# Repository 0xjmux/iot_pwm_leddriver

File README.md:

# IoT driver for "Dumb" 5050 RGB LED Strips
ESP8266-based LED Driver designed to work with WLED and cheap 12V barrel-jack power supplies for accent lighting around the home. 

This driver was designed to allow network-enabled control of almost any 12V "dumb" strip around, from plain white to FCOB strips to RGBW. 

My v1.0 worked perfectly, so I'm going to leave it as-is. The only upgrades I'd make at this point are: 
1) WLED announced that they're deprecating ESP8266 support right after I ordered v1.0, but for driving a single color the ESP8266 should be more than enough. 
2) There's some whine from the Power mosfet drivers, but it's barely noticable and not really worth addressing unless I was already doing a redesign. 

***See [Releases](https://github.com/0xjmux/iot_pwm_leddriver/releases) for all the necessary files and information to make your own!***

### Features
* Uses mini blade fuses for overcurrent protection and to protect against fire hazard from shorts on bad quality LED strips
* Board designed to handle up to and above maximum expected from most LED strips (8A)
* 4 channels to handle RGBW: or up to 4 single-color strips
* Terminal block for ease of use connecting strips and a 2.1mm jack allowing use of cheap 12V supplies you have lying around
* Capable of both programming and debug over [SOICbite Connector](https://github.com/SimonMerrett/SOICbite).
* Includes status and power LEDs and board overvoltage protection

* See [ABOUT.md](./ABOUT.md) for some information about design goals and the project. 

#### Pinout 

| Output     | ESP Pin |
| -----      | ------  |
| LED_R      | GPIO 5  |
| LED_G      | GPIO 13 |
| LED_B      | GPIO 14 |
| LED_W      | GPIO 12 |
| STATUS LED | GPIO 16 |

#### Case
I also designed a 3D printable case, which can be found under [case/](case/). The screw terminals are still easily accessible, and there's a window on the bottom so you can see the board name and version without having to open it. 
* The case uses M2x8mm screws to hold the two halves together, and is designed to be printed in PLA with 10% infill. 

### v1.0 - First try works!
* Complete redesign from v0.2, with a focus on overall system design and ease of setup for the end user. 
* Uses mini blade fuses for overcurrent protection and to protect against fire hazard from shorts on bad quality LED strips
* Board designed to handle up to and above maximum expected from most LED strips (8A)
* 4 channels to handle RGBW: or up to 4 single-color strips
* Terminal block for ease of use connecting strips and a 2.1mm jack allowing use of cheap 12V supplies you have lying around
* Capable of both programming and debug over [SOICbite Connector](https://github.com/SimonMerrett/SOICbite).
* Includes status and power LEDs and board overvoltage protection

### v0.1 - Quick Board Mock-up
* My first 4 layer board! But some improvement still possible

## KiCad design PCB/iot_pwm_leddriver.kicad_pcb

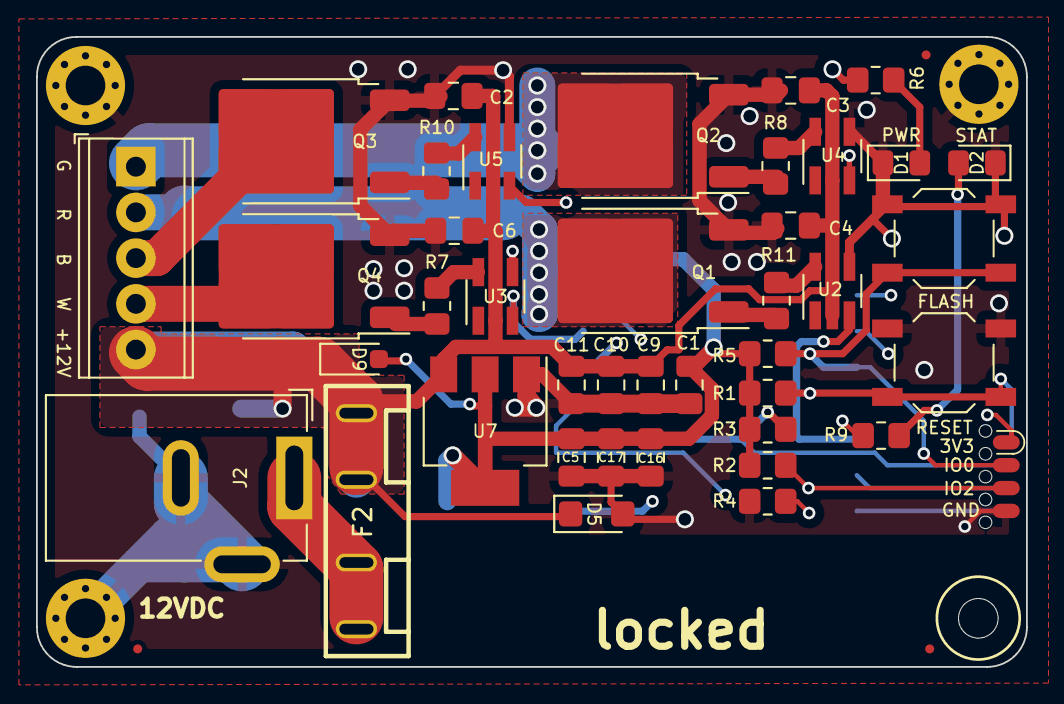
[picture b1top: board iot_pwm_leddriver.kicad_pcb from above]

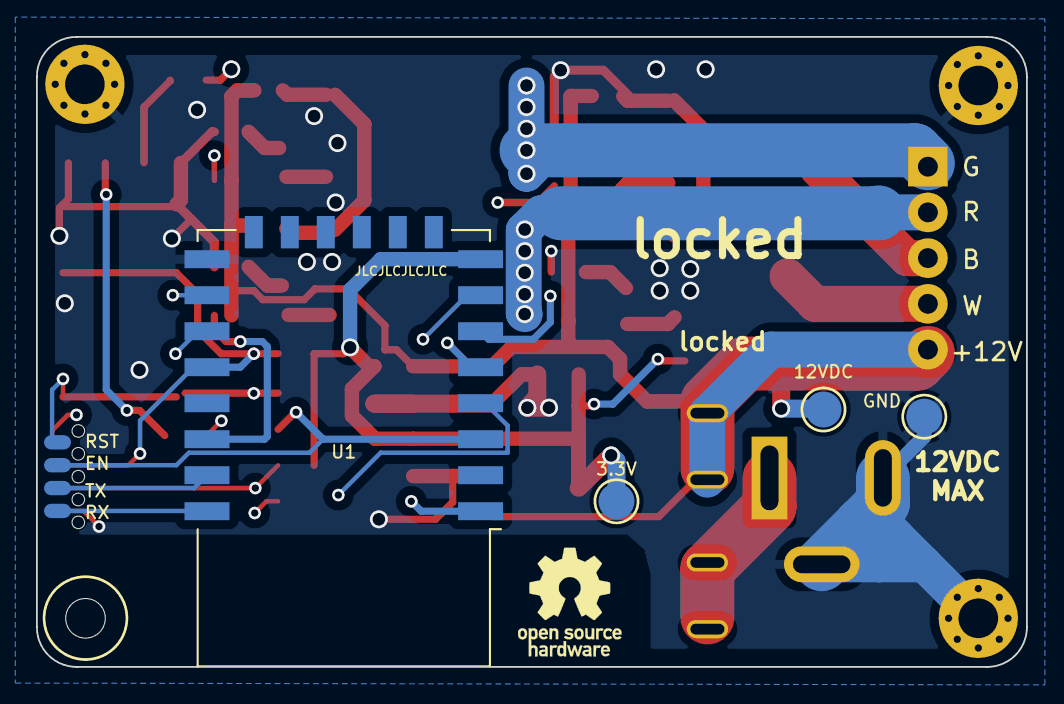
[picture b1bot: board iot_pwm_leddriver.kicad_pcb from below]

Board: 4 copper layers, 55.0 x 35.0 mm, 52 parts (4 on the bottom side), 30 nets.

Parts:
C1, C2, C3, C4, C5, C6, C9, C10, C11, C17: 10uF; C_0805_2012Metric_Pad1.18x1.45mm_HandSolder
C16: 100nF; C_0805_2012Metric_Pad1.18x1.45mm_HandSolder
D1: PWR; LED_0805_2012Metric_Pad1.15x1.40mm_HandSolder
D2: STAT; LED_0805_2012Metric_Pad1.15x1.40mm_HandSolder
D5: SMF12A; D_SMF
D9: 1N5819WS; D_SOD-323_HandSoldering
F2: Fuse Holder; FUSE-TH_XF-505P
FID1, FID2, FID3: Fiducial; Fiducial_0.5mm_Mask1mm
H1, H3, H4: MountingHole_Pad; MountingHole_2.2mm_M2_Pad_Via
H2: Non-via mounting hole; MountingHole_2.2mm_M2_ISO7380
J1: ProgConn-SOICBite; SOIC_clipProgESP8266
J2: 12V PWR; BarrelJack_GCT_DCJ200-10-A_Horizontal
J3: LED_GRBWA; TerminalBlock_Phoenix_MPT-0,5-5-2.54_1x05_P2.54mm_Horizontal
Q1, Q2, Q3, Q4: UMW30N06; TO-252-2
R1, R2, R3, R4, R5: 10k; R_0805_2012Metric_Pad1.20x1.40mm_HandSolder
R6, R9: 1k; R_0805_2012Metric_Pad1.20x1.40mm_HandSolder
R7, R8, R10, R11: 100; R_0805_2012Metric_Pad1.20x1.40mm_HandSolder
SW1: RESET; SW_SPST_TL3342
SW2: FLASH; SW_SPST_TL3342
TP3: 12VDC; TestPoint_Pad_D2.0mm
TP5: 3.3V; TestPoint_Pad_D2.0mm
TP6: GND; TestPoint_Pad_D2.0mm
U1: ESP-12F; ESP-12E
U2, U3, U4, U5: MCP1416; SOT-23-5_HandSoldering
U7: AMS1117-3.3; SOT-223-3_TabPin2

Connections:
+3.3V: C1.1, C5.1, C16.1, C17.1, D9.2 (A), J1.1 (VCC), R1.1, R2.1, R3.1, R5.2, R6.2, TP5.1, U1.8 (VCC), U7.2 (VO)
/12VDC IN: F2.1, J2.1
/GPIO0: J1.2 (GPIO0), R5.1, SW2.2, U1.18 (GPIO0)
/LED Driver/LED_B: U1.5 (GPIO14), U5.3 (IN)
/LED Driver/LED_B_G: Q3.1 (G), R10.2
/LED Driver/LED_B_GND: J3.3 (BK), Q3.2 (D)
/LED Driver/LED_G: U1.7 (GPIO13), U4.3 (IN)
/LED Driver/LED_G_G: Q2.1 (G), R8.2
/LED Driver/LED_G_GND: J3.1 (GK), Q2.2 (D)
/LED Driver/LED_R: U1.20 (GPIO5), U2.3 (IN)
/LED Driver/LED_R_G: Q1.1 (G), R11.2
/LED Driver/LED_R_GND: J3.2 (RK), Q1.2 (D)
/LED Driver/LED_W: U1.6 (GPIO12), U3.3 (IN)
/LED Driver/LED_W_G: Q4.1 (G), R7.2
/LED Driver/LED_W_GND: J3.4 (W), Q4.2 (D)
/RX: J1.5 (RX), U1.22 (GPIO1/TXD)
/TX: J1.6 (TX), U1.21 (GPIO3/RXD)
/~RST: J1.8 (RST), R1.2, SW1.2, U1.1 (~RST)
EN: J1.7 (CH_PD), R3.2, U1.3 (EN)
Earth: C1.2, C2.2, C3.2, C4.2, C5.2, C6.2, C9.2, C10.2, C11.2, C16.2, C17.2, D1.1 (K), D2.1 (K), D5.2 (A2), H1.1, H3.1, H4.1, J1.4 (GND), J2.2, J2.3, Q1.3 (S), Q2.3 (S), Q3.3 (S), Q4.3 (S), R4.1, SW1.1, SW2.1, TP6.1, U1.15 (GND), U2.4 (GND), U3.4 (GND), U4.4 (GND), U5.4 (GND), U7.1 (GND)
GPIO2: J1.3 (GPIO2), R2.2, U1.17 (GPIO2)
GPIO15: R4.2, U1.16 (GPIO15)
unnamed: D1.2 (A), R6.1
unnamed: D2.2 (A), R9.1
unnamed: R9.2, U1.4 (GPIO16)
unnamed: R11.1, U2.5 (OUT)
unnamed: R7.1, U3.5 (OUT)
unnamed: R8.1, U4.5 (OUT)
unnamed: R10.1, U5.5 (OUT)
VDD: C2.1, C3.1, C4.1, C6.1, C9.1, C10.1, C11.1, D5.1 (A1), D9.1 (K), F2.2, J3.5 (A), TP3.1, U2.2 (Vdd), U3.2 (Vdd), U4.2 (Vdd), U5.2 (Vdd), U7.3 (VI)

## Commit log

2023-12-23 first commit with initial PCB rev
2023-12-23 changed mounting holes to ones without fiducials and fixed power calculation
2023-12-23 added silkscreen to board and pictures to readme
2023-12-24 Redesign around new components added to scheamtic
    - shift left most of board
    - re-layout
    - new components
    - drc passes (mostly)
2023-12-26 fuse added to schematic. began board re-layout
2023-12-26 began rev2 of layout. board size will have to be increased
    - will need to make compomises regarding I/O, wont be able to make both power in and out fit on same short side :(
2024-01-08 design v1.0 - complete redesign
    * redid schematic
    * changed to screw terminal
    * added W channel for RGBW strips
    * did layout
2024-01-08 schematic and layout cleanup
    * plus BOM finalization
2024-01-12 v1.0 ordered! README updated, with everything else
    Boards were ordered. All requisite files added, and a basic README set
    up talking about the project.
2024-01-16 updates to readme and about pages
2024-01-18 small readme changes
2024-01-23 readme update
2024-02-06 detailed project readme
2024-02-06 fix image height mismatch
2024-02-06 image height again
